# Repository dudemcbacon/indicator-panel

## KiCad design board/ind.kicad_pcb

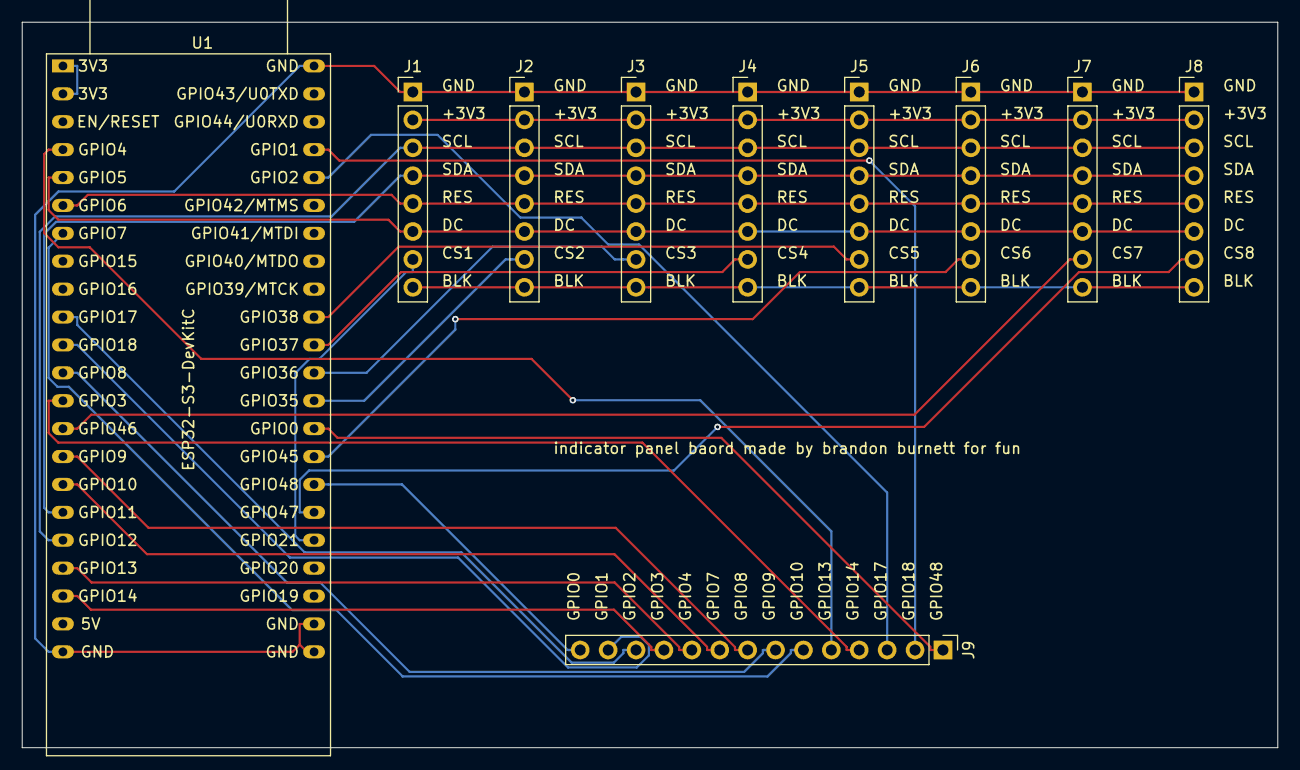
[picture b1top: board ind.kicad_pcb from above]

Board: 2 copper layers, 114.3 x 66.0 mm, 10 parts (0 on the bottom side), 30 nets.

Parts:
J1: OLED1; PinHeader_1x08_P2.54mm_Vertical
J2: OLED2; PinHeader_1x08_P2.54mm_Vertical
J3: OLED3; PinHeader_1x08_P2.54mm_Vertical
J4: OLED4; PinHeader_1x08_P2.54mm_Vertical
J5: OLED5; PinHeader_1x08_P2.54mm_Vertical
J6: OLED6; PinHeader_1x08_P2.54mm_Vertical
J7: OLED7; PinHeader_1x08_P2.54mm_Vertical
J8: OLED8; PinHeader_1x08_P2.54mm_Vertical
J9: Conn_01x14; PinHeader_1x14_P2.54mm_Vertical
U1: ESP32-S3-DevKitC

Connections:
+3.3V: U1.1 (3V3), U1.2 (3V3)
+3V3: J1.2 (VCC), J2.2 (VCC), J3.2 (VCC), J4.2 (VCC), J5.2 (VCC), J6.2 (VCC), J7.2 (VCC), J8.2 (VCC)
/BLK: J1.8 (BLK), J2.8 (BLK), J3.8 (BLK), J4.8 (BLK), J5.8 (BLK), J6.8 (BLK), J7.8 (BLK), J8.8 (BLK)
/CS1: J1.7 (CS), U1.27 (GPIO21)
/CS2: J2.7 (CS), U1.32 (GPIO35)
/CS3: J3.7 (CS), U1.33 (GPIO36)
/CS4: J4.7 (CS), U1.34 (GPIO37)
/CS5: J5.7 (CS), U1.35 (GPIO38)
/CS6: J6.7 (CS), U1.30 (GPIO45)
/CS7: J7.7 (CS), U1.14 (GPIO46)
/CS8: J8.7 (CS), U1.28 (GPIO47)
/DC: J1.6 (DC), J2.6 (DC), J3.6 (DC), J4.6 (DC), J5.6 (DC), J6.6 (DC), J7.6 (DC), J8.6 (DC), U1.5 (GPIO5/ADC1_CH4)
/GPIO0: J9.1, U1.31 (GPIO0)
/GPIO1: J9.2, U1.41 (GPIO1/ADC1_CH0)
/GPIO2: J9.3, U1.40 (GPIO2/ADC1_CH1)
/GPIO3: J9.4, U1.13 (GPIO3/ADC1_CH2)
/GPIO4: J9.5, U1.4 (GPIO4/ADC1_CH3)
/GPIO7: J9.6, U1.7 (GPIO7/ADC1_CH6)
/GPIO8: J9.7, U1.12 (GPIO8/ADC1_CH7)
/GPIO9: J9.8, U1.15 (GPIO9/ADC1_CH8)
/GPIO10: J9.9, U1.16 (GPIO10/ADC1_CH9)
/GPIO13: J9.10, U1.19 (GPIO13/ADC2_CH2)
/GPIO14: J9.11, U1.20 (GPIO14/ADC2_CH3)
/GPIO17: J9.12, U1.10 (GPIO17/ADC2_CH6)
/GPIO18: J9.13, U1.11 (GPIO18/ADC2_CH7)
/GPIO48: J9.14, U1.29 (GPIO48)
/RES: J1.5 (RES), J2.5 (RES), J3.5 (RES), J4.5 (RES), J5.5 (RES), J6.5 (RES), J7.5 (RES), J8.5 (RES), U1.6 (GPIO6/ADC1_CH5)
/SCL: J1.3 (SDL), J2.3 (SDL), J3.3 (SDL), J4.3 (SDL), J5.3 (SDL), J6.3 (SDL), J7.3 (SDL), J8.3 (SDL), U1.18 (GPIO12/ADC2_CH1)
/SDA: J1.4 (SDA), J2.4 (SDA), J3.4 (SDA), J4.4 (SDA), J5.4 (SDA), J6.4 (SDA), J7.4 (SDA), J8.4 (SDA), U1.17 (GPIO11/ADC2_CH0)
GND: J1.1 (GND), J2.1 (GND), J3.1 (GND), J4.1 (GND), J5.1 (GND), J6.1 (GND), J7.1 (GND), J8.1 (GND), U1.22 (GND), U1.23 (GND), U1.24 (GND), U1.44 (GND)

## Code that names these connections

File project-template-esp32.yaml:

---
# These substitutions allow the end user to override certain values
substitutions:
  name: "indicator-panel"

esphome:
  name: "${name}"
  # Automatically add the mac address to the name
  # so you can use a single firmware for all devices
  name_add_mac_suffix: true
  platformio_options:
    board_build.arduino.memory_type: qio_opi

  # This will allow for (future) project identification,
  # configuration and updates.
  project:
    name: esphome.project-template
    version: "1.0"

esp32:
  board: esp32-s3-devkitc-1
  variant: esp32s3
  flash_size: 16MB
  partitions: "default_16MB.csv"
  framework:
    type: arduino

# To be able to get logs from the device via serial and api.
logger:
  level: DEBUG

# API is a requirement of the dashboard import.
api:

wifi:
  ssid: !secret wifi_ssid
  password: !secret wifi_pass
  fast_connect: on

ota:
  platform: esphome

psram:
  mode: octal
  speed: 80MHz

color:
  - id: gray
    red: 50%
    green: 50%
    blue: 50%

font:
  - file: "gfonts://Roboto"
    id: web_font
    size: 20

spi:
  clk_pin: 12
  mosi_pin: 11

display:
  - platform: ili9xxx
    model: gc9a01a
    auto_clear_enabled: false
    id: gca901_display1
    invert_colors: false
    cs_pin: GPIO21 # CS1
    dc_pin:
      number: GPIO5
      allow_other_uses: true
    reset_pin:
      number: GPIO6
    dimensions:
      height: 240
      width: 240
    rotation: 90°
    data_rate: 20MHz
    lambda: |-
      it.print(50, 50, id(web_font), "kill me1!");
  - platform: ili9xxx
    model: gc9a01a
    auto_clear_enabled: false
    id: gca901_display2
    invert_colors: false
    cs_pin: GPIO48 # CS2
    dc_pin:
      number: GPIO5
      allow_other_uses: true
    dimensions:
      height: 240
      width: 240
    rotation: 90°
    data_rate: 20MHz
    lambda: |-
      it.print(50, 50, id(web_font), "kill me2!");
  - platform: ili9xxx
    model: gc9a01a
    auto_clear_enabled: false
    id: gca901_display3
    invert_colors: false
    cs_pin: GPIO18 # CS3
    dc_pin:
      number: GPIO5
      allow_other_uses: true
    dimensions:
      height: 240
      width: 240
    rotation: 90°
    data_rate: 20MHz
    lambda: |-
      it.print(50, 50, id(web_font), "kill me3!");
  - platform: ili9xxx
    model: gc9a01a
    auto_clear_enabled: false
    id: gca901_display4
    invert_colors: false
    cs_pin: GPIO17 # CS4
    dc_pin:
      number: GPIO5
      allow_other_uses: true
    dimensions:
      height: 240
      width: 240
    rotation: 90°
    data_rate: 20MHz
    lambda: |-
      it.print(50, 50, id(web_font), "kill me4!");
  - platform: ili9xxx
    model: gc9a01a
    auto_clear_enabled: false
    id: gca901_display5
    invert_colors: false
    cs_pin: GPIO38 # CS5
    dc_pin:
      number: GPIO5
      allow_other_uses: true
    dimensions:
      height: 240
      width: 240
    rotation: 90°
    data_rate: 20MHz
    lambda: |-
      it.print(50, 50, id(web_font), "kill me5!");
  - platform: ili9xxx
    model: gc9a01a
    auto_clear_enabled: false
    id: gca901_display6
    invert_colors: false
    cs_pin: GPIO45 # CS6
    dc_pin:
      number: GPIO5
      allow_other_uses: true
    dimensions:
      height: 240
      width: 240
    rotation: 90°
    data_rate: 20MHz
    lambda: |-
      it.print(50, 50, id(web_font), "kill me6!");
  - platform: ili9xxx
    model: gc9a01a
    auto_clear_enabled: false
    id: gca901_display7
    invert_colors: false
    cs_pin: GPIO46 # CS7
    dc_pin:
      number: GPIO5
      allow_other_uses: true
    dimensions:
      height: 240
      width: 240
    rotation: 90°
    data_rate: 20MHz
    lambda: |-
      it.print(50, 50, id(web_font), "kill me7!");
  - platform: ili9xxx
    model: gc9a01a
    auto_clear_enabled: false
    id: gca901_display8
    invert_colors: false
    cs_pin: GPIO47 # CS8
    dc_pin:
      number: GPIO5
      allow_other_uses: true
    dimensions:
      height: 240
      width: 240
    rotation: 90°
    data_rate: 20MHz
    lambda: |-
      it.print(50, 50, id(web_font), "kill me8!");
#  - platform: ili9xxx
#    model: gc9a01a
#    auto_clear_enabled: false
#    id: gca901_display9
#    cs_pin: GPIO18  # CS9
#    dc_pin:
#      number: GPIO5
#      allow_other_uses: true
#    dimensions:
#      height: 240
#      width: 240
#    rotation: 90°
#    data_rate: 20MHz
#    lambda: |-
#      it.print(50, 50, id(web_font), "kill me9!");

output:
  - id: led_1_output
    platform: gpio
    pin: GPIO3
  - id: led_2_output
    platform: gpio
    pin: GPIO15
  - id: led_3_output
    platform: gpio
    pin: GPIO13
  - id: led_4_output
    platform: gpio
    pin: GPIO10
  - id: led_5_output
    platform: gpio
    pin: GPIO9
  - id: led_6_output
    platform: gpio
    pin: GPIO8
  - id: led_7_output
    platform: gpio
    pin: GPIO7
  - id: led_8_output
    platform: gpio
    pin: GPIO4

light:
  - platform: binary
    id: led_1
    name: led_1
    restore_mode: ALWAYS_ON
    output: led_1_output
  - platform: binary
    id: led_2
    name: led_2
    restore_mode: ALWAYS_ON
    output: led_2_output
  - platform: binary
    id: led_3
    name: led_3
    restore_mode: ALWAYS_ON
    output: led_3_output
  - platform: binary
    id: led_4
    name: led_4
    restore_mode: ALWAYS_ON
    output: led_4_output
  - platform: binary
    id: led_5
    name: led_5
    restore_mode: ALWAYS_ON
    output: led_5_output
  - platform: binary
    id: led_6
    name: led_6
    restore_mode: ALWAYS_ON
    output: led_6_output
  - platform: binary
    id: led_7
    name: led_7
    restore_mode: ALWAYS_ON
    output: led_7_output
  - platform: binary
    id: led_8
    name: led_8
    restore_mode: ALWAYS_ON
    output: led_8_output

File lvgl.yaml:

# Before asking any questions - read the docs!: https://deploy-preview-3510--esphome.netlify.app/components/lvgl.html

esphome:
  name: t-embed
  friendly_name: LVGL Test on T-Embed
  platformio_options:
    board_build.flash_mode: dio

esp32:
  board: esp32-s3-devkitc-1
  variant: esp32s3
  framework:
    type: esp-idf

logger:
  level: DEBUG
  hardware_uart: USB_SERIAL_JTAG

wifi:
  ssid: Awesome.
  password: baconsandwich!12345
  fast_connect: on

external_components:
 - source: github://clydebarrow/esphome@lvgl_original
   components: [ lvgl ] 

power_supply:
  - id: power_on
    enable_on_boot: true
    pin:
      ignore_strapping_warning: true
      number: GPIO46

spi:
  clk_pin: GPIO12
  mosi_pin: GPIO11
  interface: hardware

output:
  - platform: ledc
    pin:
      number: GPIO15
    id: backlight_output

light:
  - platform: monochromatic
    output: backlight_output
    name: LCD Backlight
    id: led
    restore_mode: ALWAYS_ON
    default_transition_length: 0s

display:
  - platform: ili9xxx
    id: lcd_display
    model: st7789v
    dimensions:
      height: 170
      width: 320
      offset_height: 35
      offset_width: 0
    transform:
      swap_xy: true
      mirror_x: false
      mirror_y: true
    data_rate: 80MHz
    cs_pin: 10
    dc_pin: GPIO13
    reset_pin: GPIO9
    update_interval: never
    auto_clear_enabled: false
    invert_colors: true

sensor:
  - platform: rotary_encoder
    name: "Rotary Encoder"
    id: encoder
    pin_a: 2
    pin_b: 1
    internal: true

binary_sensor:
  - platform: gpio
    id: pushbutton
    name: Pushbutton
    pin:
      number: 0
      inverted: true
      ignore_strapping_warning: true

time:
  - platform: sntp
    id: time_comp
    on_time_sync:
      then:
        - script.execute: time_update

script:
  - id: time_update
    then:
      - lvgl.indicator.line.update:
          id: minute_hand
          value: !lambda |-
            return id(time_comp).now().minute;
      - lvgl.indicator.line.update:
          id: hour_hand
          value: !lambda |-
            auto now = id(time_comp).now();
            return std::fmod(now.hour, 12) * 60 + now.minute;
      - lvgl.label.update:
          id: date_label
          text: !lambda |-
            static const char * const mon_names[] = {"JAN", "FEB", "MAR", "APR", "MAY", "JUN", "JUL", "AUG", "SEP", "OCT", "NOV", "DEC"};
            static char date_buf[8];
            auto now = id(time_comp).now();
            snprintf(date_buf, sizeof(date_buf), "%s %2d", mon_names[now.month-1], now.day_of_month);
            return date_buf;
      - lvgl.label.update:
          id: day_label
          text: !lambda |-
            static const char * const day_names[] = {"SUN", "MON", "TUE", "WED", "THU", "FRI", "SAT"};
            return day_names[id(time_comp).now().day_of_week-1];

interval:
  - interval: 1min
    then:
      - script.execute: time_update

lvgl:
  log_level: INFO
  rotary_encoders:
    sensor: encoder
    binary_sensor: pushbutton
    group: general
  color_depth: 16
  bg_color: 0x0F0F0F
  text_font: unscii_8
  align: center
  style_definitions:
    - id: date_style
      text_font: unscii_8
      align: center
      text_color: 0x000000
      bg_opa: cover
      radius: 4
      pad_all: 2
  widgets:
    - obj: # Clock container
        height: size_content
        width: size_content
        widgets:
          - meter: # Gradient color  arc
              height: 160
              width: 160
              align: center
              bg_color: 0
              scales:
                angle_range: 360
                rotation: 255
                range_from: 0
                range_to: 12
                ticks:
                  width: 35
                  count: 13
                  length: 8
                indicators:
                  - ticks:
                      local: true
                      start_value: 0
                      end_value: 12
                      color_start: 0xFF0000
                      color_end: 0x0000FF
          - meter:
              height: 160
              width: 160
              align: center
                    
              bg_opa: TRANSP
              text_color: 0xFFFFFF
              scales:
                - ticks:
                    width: 1
                    count: 61
                    length: 10
                    color: 0xFFFFFF
                  range_from: 0
                  range_to: 60
                  angle_range: 360
                  rotation: 270
                  indicators:
                    - line:
                        id: minute_hand
                        width: 3
                        color: 0xE0E0E0
                        r_mod: -1

                - 
                  angle_range: 330
                  rotation: 300
                  range_from: 1
                  range_to: 12
                  ticks:
                    width: 1
                    count: 12
                    length: 1
                    major:
                      stride: 1
                      width: 4
                      length: 8
                      color: 0xC0C0C0
                      label_gap: 6

                - angle_range: 360
                  rotation: 270
                  range_from: 0
                  range_to: 720
                  indicators:
                    - line:
                        id: hour_hand
                        width: 4
                        color: 0xA0A0A0
                        r_mod: -20
          - label:
              styles: date_style
              id: day_label
              y: -20
          - label:
              id: date_label
              styles: date_style
              y: +20

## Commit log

2024-06-16 initial
2024-06-17 Working version
2025-08-04 it lights up
